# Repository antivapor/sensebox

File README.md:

#SenseBox Theremin
One of three devices made for EECS Senior Design at UCF, Fall 2012. See http://www.eecs.ucf.edu/seniordesign/su2012fa2012/g01.

##Related 

* [uWave](https://github.com/antivapor/uwave)
* [Expandome](https://github.com/antivapor/expandome)
* [EMI-Browser](https://github.com/antivapor/emi-browser)

##License
This work is licensed under a [Creative Commons Attribution-ShareAlike 3.0 Unported License](http://creativecommons.org/licenses/by-sa/3.0/).

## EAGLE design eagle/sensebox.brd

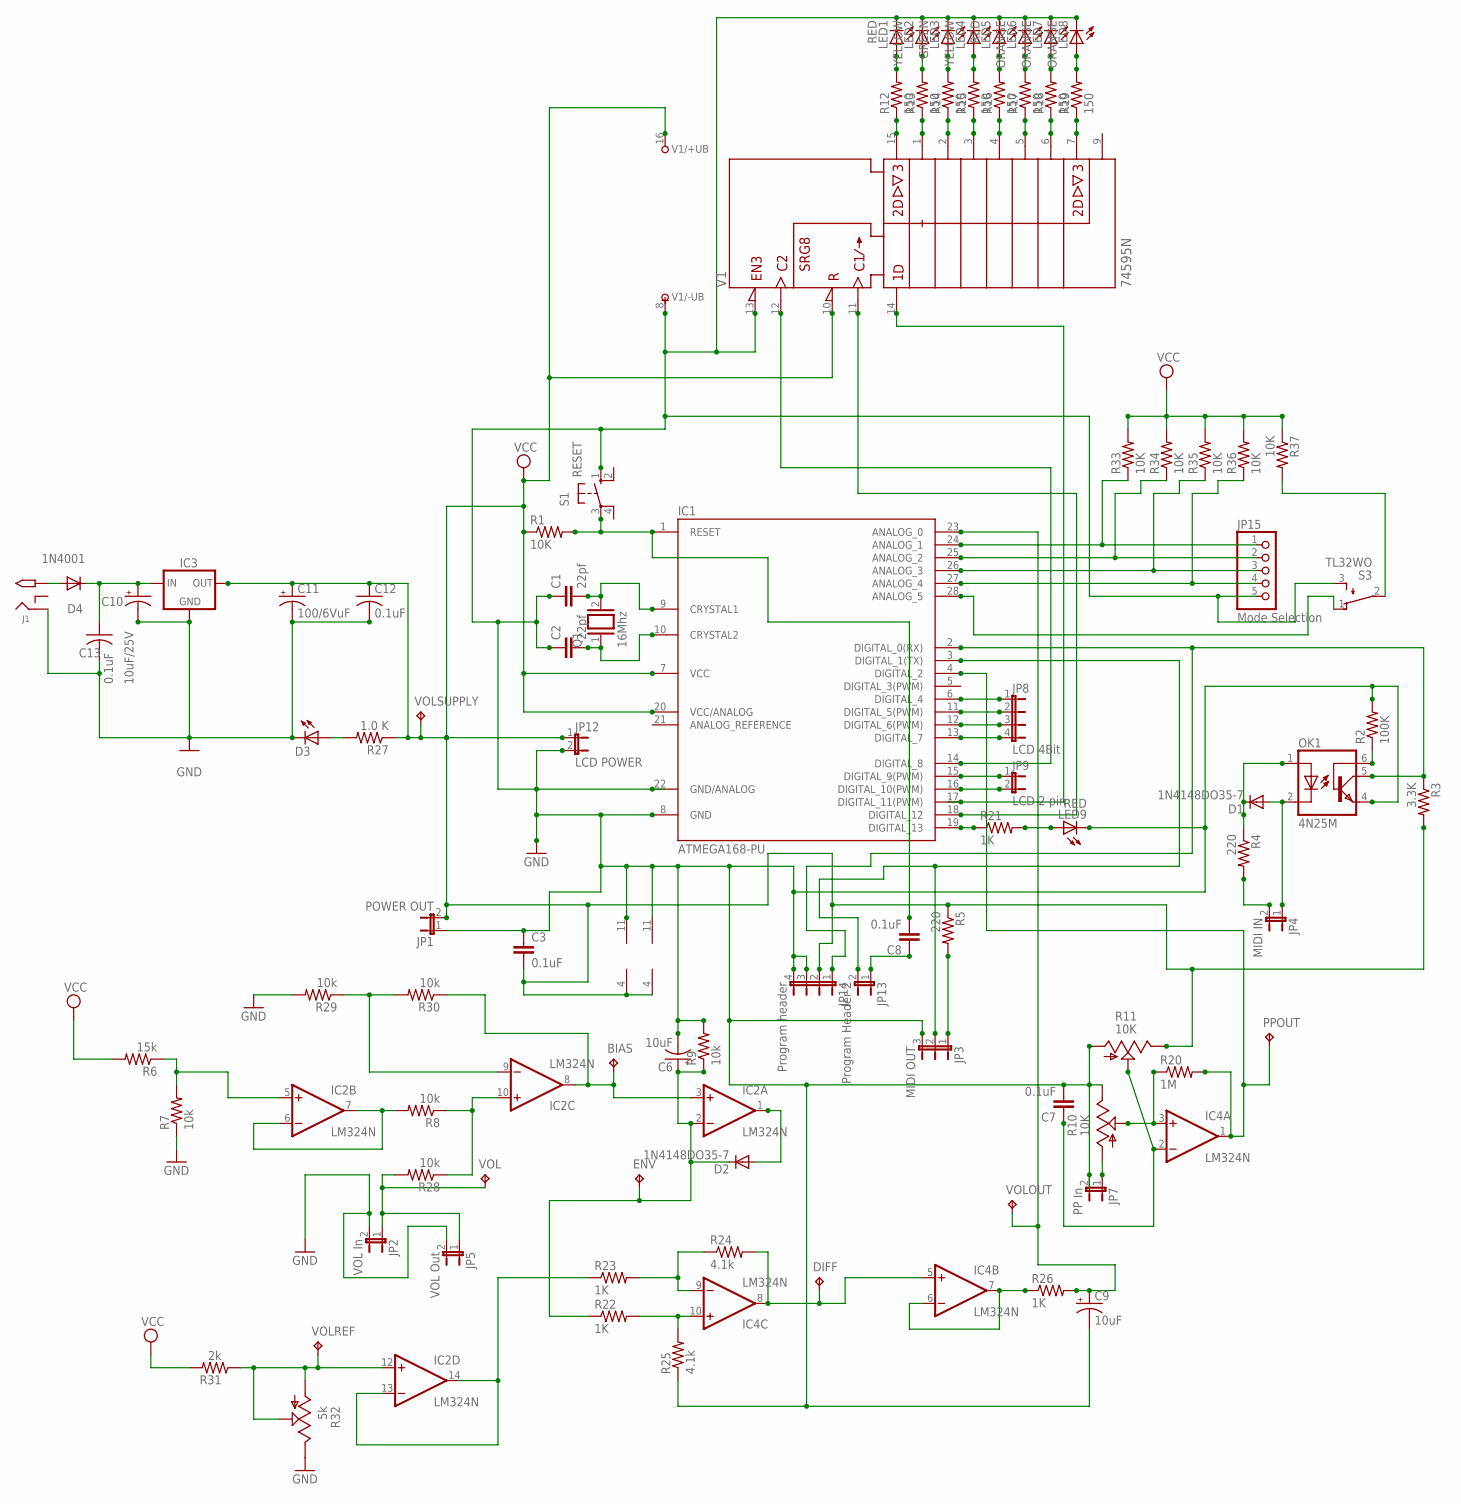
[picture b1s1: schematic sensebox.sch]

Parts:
BIAS: TP1X1
C1, C2: 22pf; C2.5-2
C3, C7: 0.1uF; C5B2.5
C6, C9: 10uF; E5-8,5
C8: 0.1uF; C2.5-2
C10: 10uF/25V; E2,5-6
C11: 100/6VuF; E2,5-6
C12, C13: 0.1uF; C025-025X050
D1, D2: 1N4148DO35-7; DO35-7
D3: GREEN; LED3MM
D4: 1N4001; DO41-10
DIFF: TP1X1
ENV: TP1X1
IC1: ATMEGA168-PU; DIL28-3
IC2, IC4: LM324N; DIL14
IC3: +5v 7805; 78XXS
J1: 2.1MMJACK; PJ-102A
JP1: POWER OUT; JP1
JP2: VOL In; JP1
JP3: MIDI OUT; JP2
JP4: MIDI IN; JP1
JP5: VOL Out; JP1
JP7: PP In; JP1
JP8: LCD 4Bit; JP4
JP9: LCD 2 pin; JP1
JP12: LCD POWER; JP1
JP13: Program Header 2; JP1
JP14: Program header; JP4
JP15: Mode Selection; 1X05
LED1, LED5, LED9: RED; LED5MM
LED2, LED4: YELLOW; LED5MM
LED3: GREEN; LED5MM
LED6, LED7, LED8: ORANGE; LED5MM
OK1: 4N25M; DIL06
PPOUT: TP1X1
Q1: 16Mhz; Q
R1, R33, R34, R35, R36, R37: 10K; 0207/7
R2: 100K; 0207/7
R3: 3.3K; 0207/7
R4, R5: 220; 0207/7
R6: 15k; 0207/10
R7, R8, R28, R29, R30: 10k; 0207/10
R9: 10k; 0207/7
R10, R11: 10K; B64Y
R12, R13, R14, R15, R16, R17, R18, R19: 150; 0207/7
R20: 1M; 0207/7
R21, R22, R23, R26: 1K; 0207/7
R24, R25: 4.1k; 0207/7
R27: 1.0 K; 0207/5V
R31: 2k; 0207/10
R32: 5k; B64Y
S1: RESET; B3F-10XX
S3: TL32WO; TL3XWO
V1: 74595N; DIL16
VOL: TP1X1
VOLOUT: TP1X1
VOLREF: TP1X1
VOLSUPPLY: TP1X1

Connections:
GND: C1.1, C2.1, C3.1, C6.-, C7.2, C9.-, C10.-, C11.-, C12.2, C13.2, D3.K (C), IC1.8 (GND), IC1.22 (GND/ANALOG), IC2.11 (V-), IC3.GND, IC4.11 (V-), J1.RING, JP1.1, JP2.2, JP3.3, JP5.2, JP7.2, JP12.2, JP14.3, JP14.4, JP15.5, LED1.K (C), LED2.K (C), LED3.K (C), LED4.K (C), LED5.K (C), LED6.K (C), LED7.K (C), LED8.K (C), LED9.K (C), OK1.4 (EMI), R2.2, R7.1, R9.2, R10.E, R11.A, R25.1, R29.2, R32.E, S1.1 (S), S3.3 (S), V1.8 (-UB), V1.13 (!G)
unnamed: C8.2, IC1.1 (RESET), R1.2, S1.3
unnamed: C1.2, IC1.9 (CRYSTAL1), Q1.2
unnamed: C2.2, IC1.10 (CRYSTAL2), Q1.1
unnamed: JP3.1, R5.2
unnamed: IC1.3 (DIGITAL_1(TX)), JP3.2, JP13.2
unnamed: D1.A, JP4.1, OK1.2 (C)
unnamed: D4.A, J1.TIP
unnamed: OK1.6 (BAS), R2.1
unnamed: IC2.5 (+IN), R6.1, R7.2
unnamed: IC1.2 (DIGITAL_0(RX)), JP14.1, OK1.5 (COL), R3.1
unnamed: JP2.1, JP5.1, R28.2, VOL.P$1
unnamed: JP7.1, R10.A
unnamed: JP4.2, R4.2
unnamed: D2.A, IC2.1 (OUT)
unnamed: C6.+, D2.C, ENV.P$1, IC2.2 (-IN), R9.1, R22.1
unnamed: IC2.10 (+IN), R8.1, R28.1
unnamed: IC4.3 (+IN), R10.S, R20.1
unnamed: C7.1, IC4.2 (-IN), R11.S
unnamed: R12.1, V1.15 (QA)
unnamed: IC1.4 (DIGITAL_2), IC4.1 (OUT), PPOUT.P$1, R20.2
unnamed: IC1.17 (DIGITAL_11(PWM)), V1.14 (SER)
unnamed: IC1.18 (DIGITAL_12), V1.11 (SRCK)
unnamed: IC1.14 (DIGITAL_8), V1.12 (RCK)
unnamed: R13.1, V1.1 (QB)
unnamed: R14.1, V1.2 (QC)
unnamed: R15.1, V1.3 (QD)
unnamed: R16.1, V1.4 (QE)
unnamed: R17.1, V1.5 (QF)
unnamed: R18.1, V1.6 (QG)
unnamed: R19.1, V1.7 (QH)
unnamed: LED1.A, R12.2
unnamed: LED2.A, R13.2
unnamed: LED3.A, R14.2
unnamed: LED4.A, R15.2
unnamed: LED5.A, R16.2
unnamed: LED6.A, R17.2
unnamed: LED7.A, R18.2
unnamed: LED8.A, R19.2
unnamed: IC1.24 (ANALOG_1), JP15.1, R33.1
unnamed: IC1.6 (DIGITAL_4), JP8.1
unnamed: IC1.11 (DIGITAL_5(PWM)), JP8.2
unnamed: IC1.12 (DIGITAL_6(PWM)), JP8.3
unnamed: IC1.13 (DIGITAL_7), JP8.4
unnamed: IC1.15 (DIGITAL_9(PWM)), JP9.1
unnamed: IC1.16 (DIGITAL_10(PWM)), JP9.2
unnamed: IC1.28 (ANALOG_5), S3.1 (O)
unnamed: IC1.25 (ANALOG_2), JP15.2, R34.1
unnamed: C8.1, JP13.1
unnamed: IC1.19 (DIGITAL_13), R21.1
unnamed: LED9.A, R21.2
unnamed: IC4.6 (-IN), IC4.7 (OUT), R26.1
unnamed: IC4.9 (-IN), R23.2, R24.1
unnamed: IC4.10 (+IN), R22.2, R25.2
unnamed: DIFF.P$1, IC4.5 (+IN), IC4.8 (OUT), R24.2
unnamed: D1.C, OK1.1 (A), R4.1
unnamed: C9.+, IC1.23 (ANALOG_0), R26.2, VOLOUT.P$1
unnamed: C10.+, C13.1, D4.C, IC3.IN
unnamed: D3.A, R27.2
unnamed: IC2.6 (-IN), IC2.7 (OUT), R8.2
unnamed: IC1.26 (ANALOG_3), JP15.3, R35.1
unnamed: IC1.27 (ANALOG_4), JP15.4, R36.1
unnamed: R37.2, S3.2
unnamed: IC2.13 (-IN), IC2.14 (OUT), R23.1
unnamed: IC2.9 (-IN), R29.1, R30.2
unnamed: BIAS.P$1, IC2.3 (+IN), IC2.8 (OUT), R30.1
unnamed: IC2.12 (+IN), R31.1, R32.A, R32.S, VOLREF.P$1
VCC: C3.2, C11.+, C12.1, IC1.7 (VCC), IC1.20 (VCC/ANALOG), IC2.4 (V+), IC3.OUT, IC4.4 (V+), JP1.2, JP12.1, JP14.2, R1.1, R3.2, R5.1, R6.2, R11.E, R27.1, R31.2, R33.2, R34.2, R35.2, R36.2, R37.1, V1.10 (!SRCLR), V1.16 (+UB), VOLSUPPLY.P$1

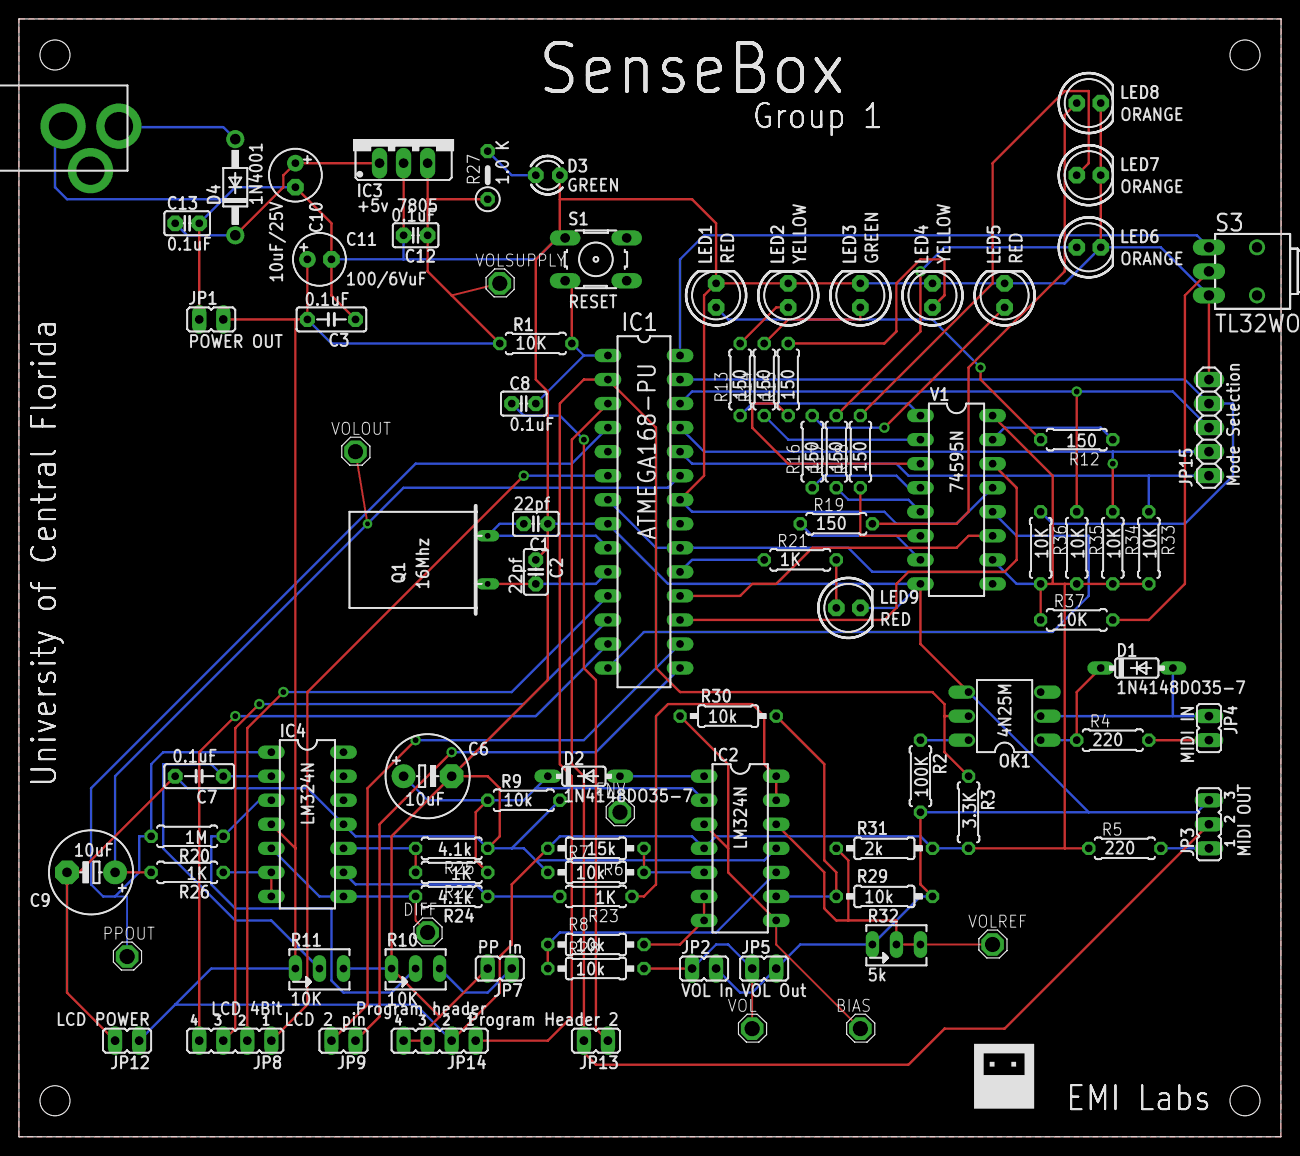
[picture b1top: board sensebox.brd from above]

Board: 2 copper layers, 133.3 x 118.1 mm, 91 parts (0 on the bottom side), 68 nets.

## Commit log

2013-01-03 eagle and gerber files
2013-01-05 image resize
2013-01-05 ruddy all caps..
